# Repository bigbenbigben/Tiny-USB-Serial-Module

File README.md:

# UIAPduino対応 CP2102N搭載 小型USBシリアル変換モジュール

[日本語](README.md) | [English](README_EN.md)

## 概要

<div class="image-row">
    
    &nbsp;&nbsp;&nbsp;&nbsp;
    
</div>

Silicon Labs社のCP2102Nを採用した、基板サイズ20mm×12mmの小型USBシリアル変換基板です。

USB Type-C接続、USBバスパワー動作に対応しており、TxD、RxDはスルーホール端子から引き出しています。

本基板は[UIAPduino Pro Micro CH32V003 V1.4](https://www.uiap.jp/uiapduino/pro-micro/ch32v003/v1dot4)のピン配置に対応しており、コンスルーやブレッドボードによりRXD、TXD、GNDをそのまま接続することができます。

## サイズ

基板サイズ：20mm×12mm
高さ：5mm（実測値）
重量：1.3g

## 特徴

- 小型です。（基板サイズ20mm×12mm）
- Silicon Labs社のCP2102Nを使用。
- 過電流保護回路搭載。
- 静電気対策回路搭載。
- USB Type-Cコネクタ搭載。
- USBバスパワー動作。
- 入力5Vトレラント。
- UIAPduinoにそのまま挿入できるピン配置になっています。
- RoHS対応です。

## 主な仕様

- 電源電圧Max.：5V
- IO電圧Max.：3.3V（入力5Vトレラント）
- ボーレートMin.：300bps
- ボーレートMax.：3Mbps
- 受信バッファ：512バイト
- 送信バッファ：512バイト
- LED 2個（電源：青、TxD：オレンジ）

## ピン配置

- p1 ： +5V(VBUS)
- p2 ： RXD
- p3 ： TXD
- p4 ： GND

## 対応OS

本製品に使用しているCP2102Nは以下のOS向けにドライバが提供されています。

対象OS：Windows, macOS, Linux, and Android

ドライバ提供サイト：[https://www.silabs.com/software-and-tools/usb-to-uart-bridge-vcp-drivers?tab=downloads](https://www.silabs.com/software-and-tools/usb-to-uart-bridge-vcp-drivers?tab=downloads)

筆者は Windows 11 Pro 25H2 で動作を確認しています。

## 注意

- RXDは5V入力対応、TXDは3.3V出力です。一般的な5Vマイコンでは問題なく使用できますが、5Vロジック入力を必須とする機器には対応していません。
- TXD/RXDの接続には注意してください。例としてUART接続では、TXDとRXDをクロス接続します。本製品のTXDを相手機器のRXDへ、本製品のRXDを相手機器のTXDへ接続してください。
- 2026/7/12現在、UIAPduinoは`Serial.available()`が動かないようです。筆者は[UIAPSerial](https://github.com/tarosay/sdlog_uiapduino/tree/main/SDLog)というライブラリで動作確認しました。

## Author

ポジティブフィードバック
bigben (@bigbenbigben)

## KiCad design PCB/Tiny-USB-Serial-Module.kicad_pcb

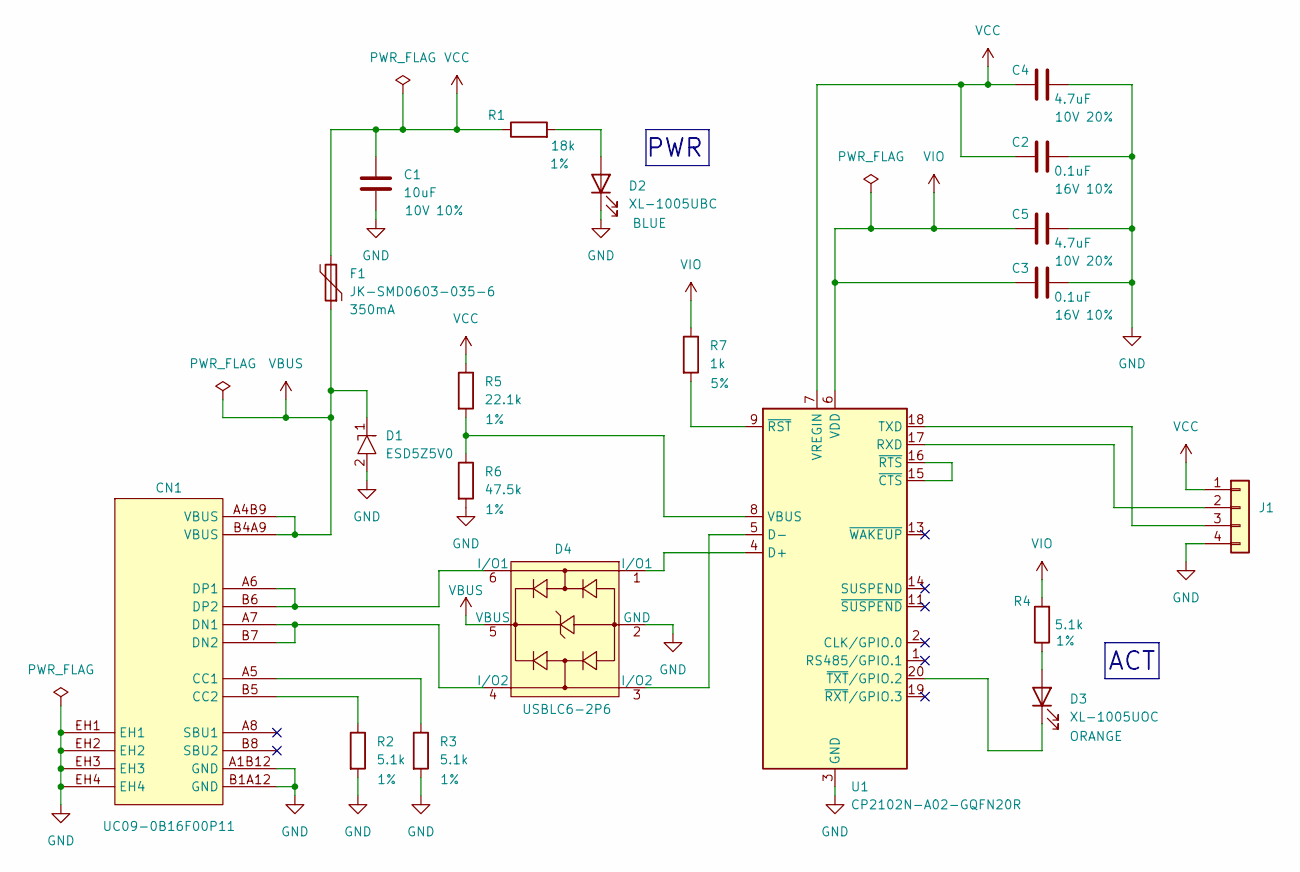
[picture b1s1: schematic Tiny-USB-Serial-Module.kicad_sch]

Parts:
C1: 10uF; C_0603_1608Metric; PART CL10A106KP8NNNC; LCSC Part # C19702
C2, C3: 0.1uF; C_0402_1005Metric; PART CL05B104KO5NNNC; LCSC Part # C1525
C4, C5: 4.7uF; C_0402_1005Metric; PART CL05A475MP5NRNC; LCSC Part # C23733
CN1: UC09-0B16F00P11; USB_C_Receptacle_UC09-0B16F00P11; PART UC09-0B16F00P11; LCSC Part # C36936538
D1: ESD5Z5V0; D_SOD-523; PART ESD5Z5V0; LCSC Part # C85708
D2: XL-1005UBC; LED_0402_1005Metric; PART XL-1005UBC; LCSC Part # C22355736
D3: XL-1005UOC; LED_0402_1005Metric; PART XL-1005UOC; LCSC Part # C965791
D4: USBLC6-2P6; SOT-666; PART USBLC6-2P6; LCSC Part # C15999
F1: JK-SMD0603-035-6; Fuse_0603_1608Metric; PART JK-SMD0603-035-6; LCSC Part # C2832202
J1: Conn_01x04; Pad_1x04_P2.54mm
R1: 18k; R_0603_1608Metric; PART 0603WAF1802T5E; LCSC Part # C25810
R2, R3, R4: 5.1k; R_0402_1005Metric; PART 0402WGF5101TCE; LCSC Part # C25905
R5: 22.1k; R_0402_1005Metric; PART RTT022212FTH; LCSC Part # C102896
R6: 47.5k; R_0402_1005Metric; PART CR0402FF4752G; LCSC Part # C100449
R7: 1k; R_0402_1005Metric; PART 0402WGF1001TCE; LCSC Part # C11702
U1: CP2102N-A02-GQFN20R; SiliconLabs_QFN-20-1EP_3x3mm_P0.5mm_EP1.8x1.8mm; PART CP2102N-A02-GQFN20R; LCSC Part # C969913

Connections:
GND: C1.2, C2.2, C3.2, C4.2, C5.2, CN1.A1B12 (GND), CN1.B1A12 (GND), CN1.EH1, CN1.EH2, CN1.EH3, CN1.EH4, D1.2 (A), D2.1 (K), D4.2 (GND), J1.4, R2.2, R3.2, R6.2, U1.3 (GND), U1.12 (GND), U1.21 (GND)
unnamed: CN1.A5 (CC1), R3.1
unnamed: CN1.B5 (CC2), R2.1
unnamed: CN1.A7 (DN1), CN1.B7 (DN2), D4.4 (I/O2)
unnamed: CN1.A6 (DP1), CN1.B6 (DP2), D4.6 (I/O1)
unnamed: D2.2 (A), R1.2
unnamed: D3.2 (A), R4.1
unnamed: D3.1 (K), U1.20 (~TXT/GPIO.2)
unnamed: J1.2, U1.17 (RXD)
unnamed: J1.3, U1.18 (TXD)
unnamed: D4.1 (I/O1), U1.4 (D+)
unnamed: D4.3 (I/O2), U1.5 (D-)
unnamed: R5.2, R6.1, U1.8 (VBUS)
unnamed: U1.15 (~CTS), U1.16 (~RTS)
unnamed: R7.2, U1.9 (~RST)
VBUS: CN1.A4B9 (VBUS), CN1.B4A9 (VBUS), D1.1 (K), D4.5 (VBUS), F1.1
VCC: C1.1, C2.1, C4.1, F1.2, J1.1, R1.1, R5.1, U1.7 (VREGIN)
VIO: C3.1, C5.1, R4.2, R7.1, U1.6 (VDD)

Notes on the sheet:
ACT
PWR

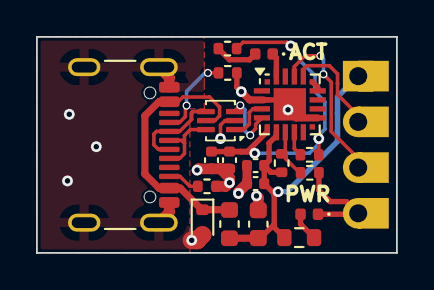
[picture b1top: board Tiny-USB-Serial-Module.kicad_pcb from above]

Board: 2 copper layers, 20.0 x 12.0 mm, 20 parts (0 on the bottom side), 18 nets.

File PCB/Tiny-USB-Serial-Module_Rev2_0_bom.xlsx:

Tiny-USB-Serial-Module BOM
Rev | 2
June 7, 2026 at 15:00
Reference | Qty | PART | Value | VAL1 | VAL2 | LCSC Part #
C1 | 1 | CL10A106KP8NNNC | 10uF | 10V | 0.1 | C19702
C2,C3 | 2 | CL05B104KO5NNNC | 0.1uF | 16V | 0.1 | C1525
C4,C5 | 2 | CL05A475MP5NRNC | 4.7uF | 10V | 0.2 | C23733
CN1 | 1 | UC09-0B16F00P11 | UC09-0B16F00P11 |  |  | C36936538
D1 | 1 | ESD5Z5V0 | ESD5Z5V0 |  |  | C85708
D2 | 1 | XL-1005UBC | XL-1005UBC | BLUE |  | C22355736
D3 | 1 | XL-1005UOC | XL-1005UOC | ORANGE |  | C965791
D4 | 1 | USBLC6-2P6 | USBLC6-2P6 |  |  | C15999
F1 | 1 | JK-SMD0603-035-6 | JK-SMD0603-035-6 | 350mA |  | C2832202
R1 | 1 | 0603WAF1802T5E | 18k | 0.01 |  | C25810
R2,R3,R4 | 3 | 0402WGF5101TCE | 5.1k | 0.01 |  | C25905
R5 | 1 | RTT022212FTH | 22.1k | 0.01 |  | C102896
R6 | 1 | CR0402FF4752G | 47.5k | 0.01 |  | C100449
R7 | 1 | 0402WGF1001TCE | 1k | 0.05 |  | C11702
U1 | 1 | CP2102N-A02-GQFN20R | CP2102N-A02-GQFN20R |  |  | C969913
